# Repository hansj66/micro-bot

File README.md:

# Micro:bit sumo robot
Firmware and hardware design files for the [TimeExpander.com](https://www.timeexpander.com/) Micro:bit based robot

The bot features two motor bridges, 3 x time of flight sensors, 4 x reflective object sensors and a GPIO Expander. 

Toolchain for building the firmware is the mBed online compiler.

You can watch one of the demo state machines in action here: https://youtu.be/_6B225iNg58

# V3
There is an untested v3 in the Hardware folder. [See v3 Readme](https://github.com/rosmo-robot/micro-bot/tree/master/Hardware/V3#readme)

# V2

This is the latest tested version.

# v2 Bill of materials
* 1 x Main PCB (https://github.com/hansj66/micro-bot/blob/master/Hardware/minisumo_v2.brd)
* 4 x line sensor PCBs (https://github.com/hansj66/micro-bot/blob/master/Hardware/minisumo_sensor.brd)
* 2 x Wheels (AliExpress)
* 2 x N20 motors (AliExpress)
* 2 x N20 motor bracket assembly (AliExpress)
* 3 x VL53L0X time of flight sensors on a carrier PCB (AliExpress)
* 1 x TCA9539 IO expander (Digikey)
* 1 x TXB0106PWR Bi-directional level translator  (Digikey)
* 4 x QRE1113GR Reflective optical sensors  (Digikey)
* 1 x 100uF aluminium capacitor
* 1 x 2x5 pin 2.54mm female header (Digikey)
* 1 x battery pack for 4x AAA  (Digikey)
* 1 x JS202011SCQN slide switch  (Digikey)
* 1 x SOT223 LM1117 3.3V regulator (Digikey)
* 1 x Mini caster assembly (AliExpress + 3D printed bracket)
* 2 x 3D printed spacers (between motors and PCB)
* 1 x 12 pin male breakaway header  (Digikey)
* 3 x 6 pin RA breakaway header  (Digikey)
* 1 x hook and loop tape (for attaching battery pack)
* 2 x 100nf capacitors (motor noise suppression)

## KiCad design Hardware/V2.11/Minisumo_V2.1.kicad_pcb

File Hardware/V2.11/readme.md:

## Rosmo:bot

* Derived from [@hansj66 board](https://github.com/rosmo-robot/micro-bot)
* Adds footprint for screw terminal for power in
* Board in Kicad 6
* Encoders added to support [Bringsmart GB12-N20B](http://www.bringsmart.com/pd.jsp?id=154) Available [from Aliexpress](https://www.aliexpress.com/item/1005002307903318.html)
* TOF pins changed to support [Breakout garden TOF sensors](https://shop.pimoroni.com/collections/breakout-garden?q=tof)
* Uses screw terminal block for power
* Intended for use with Micro:bit or [Feather:bit](https://github.com/rosmo-robot/Feather-Bit/tree/main/v1)

## Parts
* Wheels https://www.aliexpress.com/item/4000099589318.html
* N20 mount https://www.aliexpress.com/item/1005001872298274.html
* N20 https://www.aliexpress.com/item/1005002307903318.html
* Powerbank https://www.aliexpress.com/item/1005002635531425.html
* Battery https://www.aliexpress.com/item/1005004385519421.html?

### Possible future development

* Use https://www.sparkfun.com/products/9453
* Use https://www.aliexpress.com/item/1005003985685357.html / https://www.aliexpress.com/item/1005003879181886.html

### Firmware to investigate

- https://github.com/Ezward/Esp32CameraRover2
- https://github.com/platisd/smartcar_shield/
- https://github.com/robokoding/sumorobot-firmware
- https://github.com/hadabot/

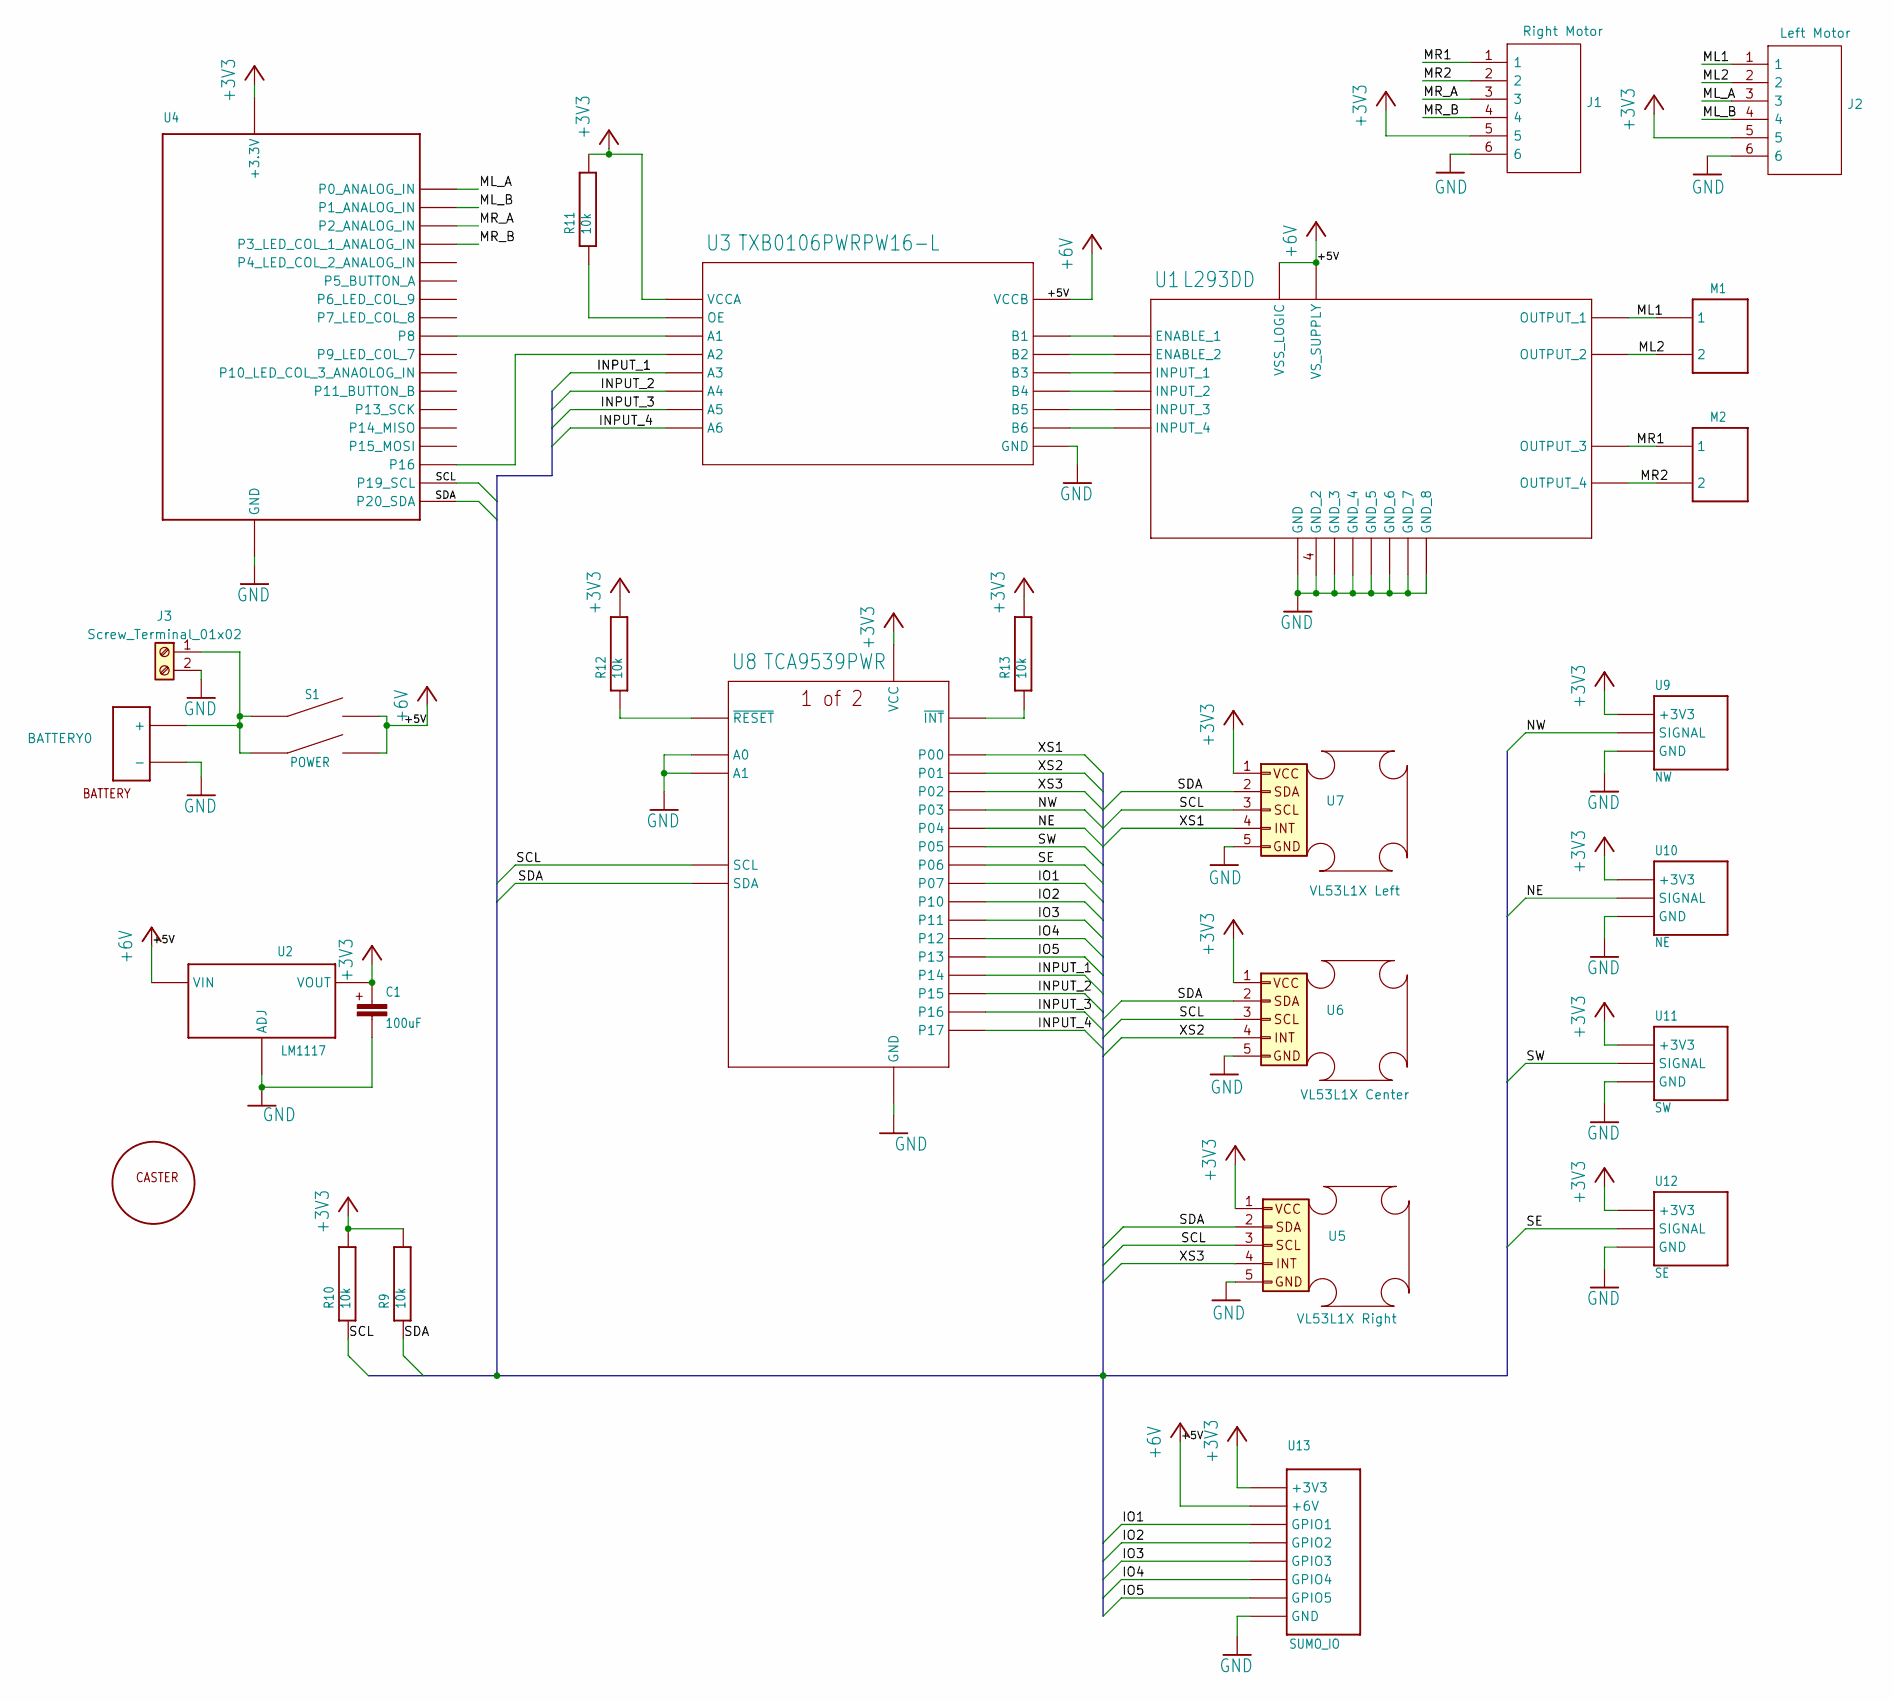
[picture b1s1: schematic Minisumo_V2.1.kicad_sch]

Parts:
BATTERY0: BATTERY_HOLDER_AAA_2X2
C1: 100uF; ALUMINUM_WURTH_100UF_865080243007
J1: Right Motor; SHDR6W50P0X200_1X6_1390X450X600P; Manufacturer_Part_Number B6B-PH-K(LF)(SN)
J2: Left Motor; SHDR6W50P0X200_1X6_1390X450X600P; Manufacturer_Part_Number B6B-PH-K(LF)(SN)
J3: Screw_Terminal_01x02; TerminalBlock_Phoenix_PT-1,5-2-3.5-H_1x02_P3.50mm_Horizontal
M1, M2: N20_MOTOR; N20-MOTOR-BRACKET
R9, R10, R11, R12, R13: 10k; RES_0402
S1: POWER; SWITCH_JS202011SCQN
U1: L293DD; SO-20
U2: LM1117; SOT-223
U3: TXB0106PWRPW16-L; PW16-L
U4: BBC Micro:bit; CYCLONE_MICROBIT_VERTICAL
U5: VL53L1X Right; VL53L1x_1x05_P2.54mm_Horizontal
U6: VL53L1X Center; VL53L1x_1x05_P2.54mm_Horizontal
U7: VL53L1X Left; VL53L1x_1x05_P2.54mm_Horizontal
U8: TCA9539PWR; 24-TSSOP
U9: NW; QRE1113_MODULE
U10: NE; QRE1113_MODULE
U11: SW; QRE1113_MODULE
U12: SE; QRE1113_MODULE
U13: SUMO_IO
U$1: CASTER

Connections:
+3V3: C1.+, J1.5, J2.5, R9.P$2, R10.P$2, R11.P$2, R12.P$2, R13.P$2, U2.P$2 (VOUT), U2.VOUT$1 (VOUT), U3.2 (VCCA), U4.3.3V@9 (+3.3V), U4.3.3V@10 (+3.3V), U4.3.3V@11 (+3.3V), U4.3.3V@12 (+3.3V), U4.3.3V@13 (+3.3V), U4.3.3V@14 (+3.3V), U5.1, U6.1, U7.1, U8.24 (VCC), U9.+3V3, U10.+3V3, U11.+3V3, U12.+3V3, U13.3V3 (+3V3)
+5V: S1.3 (B2), S1.6 (B1), U1.10 (VS_SUPPLY), U1.20 (VSS_LOGIC), U2.VIN, U3.15 (VCCB), U13.6V (+6V)
/INPUT_1: U3.4 (A3), U8.17 (P14)
/INPUT_2: U3.5 (A4), U8.18 (P15)
/INPUT_3: U3.6 (A5), U8.19 (P16)
/INPUT_4: U3.7 (A6), U8.20 (P17)
/IO1: U8.11 (P07), U13.GPIO1
/IO2: U8.13 (P10), U13.GPIO2
/IO3: U8.14 (P11), U13.GPIO3
/IO4: U8.15 (P12), U13.GPIO4
/IO5: U8.16 (P13), U13.GPIO5
/ML1: J2.1, M1.1, U1.3 (OUTPUT_1)
/ML2: J2.2, M1.2, U1.8 (OUTPUT_2)
/ML_A: J2.3, U4.P0_ANALOG_IN@36 (P0_ANALOG_IN), U4.P0_ANALOG_IN@37 (P0_ANALOG_IN), U4.P0_ANALOG_IN@38 (P0_ANALOG_IN), U4.P0_ANALOG_IN@39 (P0_ANALOG_IN)
/ML_B: J2.4, U4.P1_ANALOG_IN@28 (P1_ANALOG_IN), U4.P1_ANALOG_IN@29 (P1_ANALOG_IN), U4.P1_ANALOG_IN@30 (P1_ANALOG_IN), U4.P1_ANALOG_IN@31 (P1_ANALOG_IN)
/MR1: J1.1, M2.1, U1.13 (OUTPUT_3)
/MR2: J1.2, M2.2, U1.18 (OUTPUT_4)
/MR_A: J1.3, U4.P2_ANALOG_IN@19 (P2_ANALOG_IN), U4.P2_ANALOG_IN@20 (P2_ANALOG_IN), U4.P2_ANALOG_IN@21 (P2_ANALOG_IN), U4.P2_ANALOG_IN@22 (P2_ANALOG_IN)
/MR_B: J1.4, U4.P3_LED_COL_1_ANALOG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
/NE: U8.8 (P04), U10.SIGNAL
/NW: U8.7 (P03), U9.SIGNAL
/SCL: R10.P$1, U4.P21_SCL (P19_SCL), U5.3, U6.3, U7.3, U8.22 (SCL)
/SDA: R9.P$1, U4.P20_SDA, U5.2, U6.2, U7.2, U8.23 (SDA)
/SE: U8.10 (P06), U12.SIGNAL
/SW: U8.9 (P05), U11.SIGNAL
/XS1: U7.4, U8.4 (P00)
/XS2: U6.4, U8.5 (P01)
/XS3: U5.4, U8.6 (P02)
GND: BATTERY0.-, C1.-, J1.6, J2.6, J3.2, U1.4 (GND_2), U1.5 (GND_3), U1.6 (GND_4), U1.7 (GND_5), U1.14 (GND_6), U1.15 (GND_7), U1.16 (GND_8), U1.17 (GND), U2.GND (ADJ), U3.9 (GND), U4.GND@1 (GND), U4.GND@2 (GND), U4.GND@3 (GND), U4.GND@4 (GND), U4.GND@5 (GND), U4.GND@6 (GND), U5.5, U6.5, U7.5, U8.2 (A1), U8.12 (GND), U8.21 (A0), U9.GND, U10.GND, U11.GND, U12.GND, U13.GND
unnamed: BATTERY0.+, J3.1, S1.2 (A2), S1.5 (A1)
unnamed: R11.P$1, U3.8 (OE)
unnamed: R12.P$1, U8.3 (~RESET)
unnamed: R13.P$1, U8.1 (~INT)
unnamed: U1.1 (ENABLE_1), U3.16 (B1)
unnamed: U1.2 (INPUT_1), U3.13 (B3)
unnamed: U1.9 (INPUT_2), U3.12 (B4)
unnamed: U1.11 (ENABLE_2), U3.14 (B2)
unnamed: U1.12 (INPUT_3), U3.11 (B5)
unnamed: U1.19 (INPUT_4), U3.10 (B6)
unnamed: U3.1 (A1), U4.P8
unnamed: U3.3 (A2), U4.P16

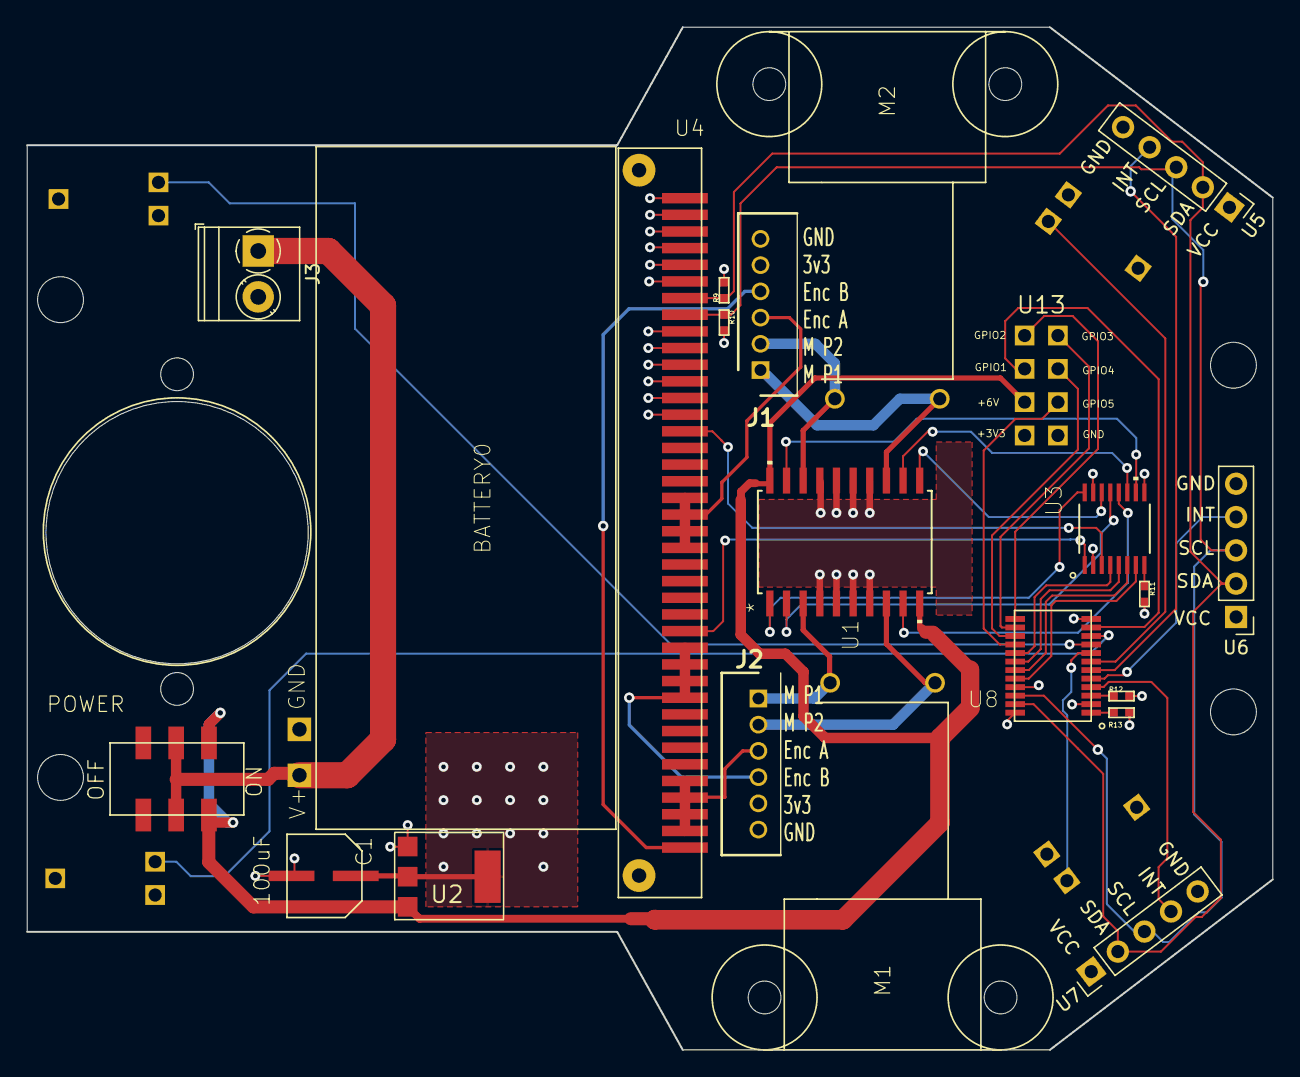
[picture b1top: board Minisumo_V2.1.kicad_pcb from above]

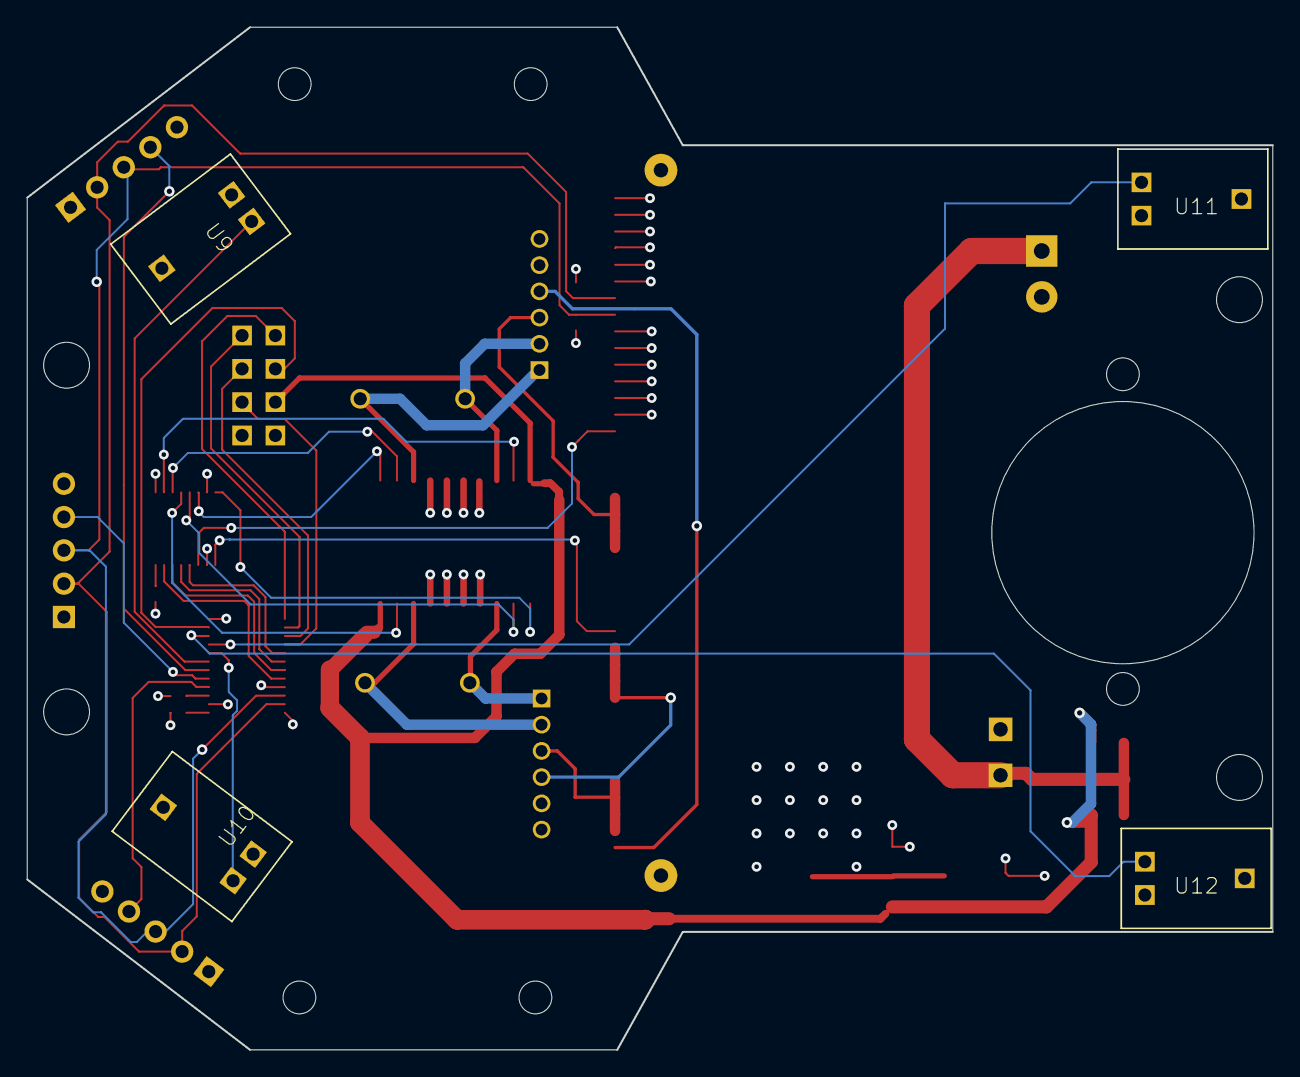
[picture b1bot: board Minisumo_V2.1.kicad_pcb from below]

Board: 4 copper layers, 95.0 x 78.0 mm, 31 parts (4 on the bottom side), 41 nets.

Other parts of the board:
@HOLE0, @HOLE1, @HOLE2, @HOLE3: (no value)

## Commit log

2020-01-03 Verified VL53L0X, QRE1113, L293DD and TXB0106
2020-01-12 Feature complete * using arduino framework
2020-02-12 Ported from arduino framework to mbed framework * Added harware selftest option on boot * Minor tweaks in Polulu VL53L0X library * Added a few visuals for the test sequence
2020-02-13 Added motor test
2020-02-13 Added range test visualization
2020-02-29 Added hardware design files. * Moved the firmware to online mbed * Added two demo state machines
2020-02-29 Added license information
2020-02-29 Removed comment regarding fixed issue
2022-09-08 kicad 6 project
2022-09-08 Zip of Kicad 6 project
2022-09-08 Added link to 2.1 documentation
2022-09-09 Zip of Kicad6 project
2022-09-09 Fix switch footprint
2022-09-10 Schematic
2022-09-18 Adds rosmo pinout
    Uses common IR sensors, uses lipo battery shield
